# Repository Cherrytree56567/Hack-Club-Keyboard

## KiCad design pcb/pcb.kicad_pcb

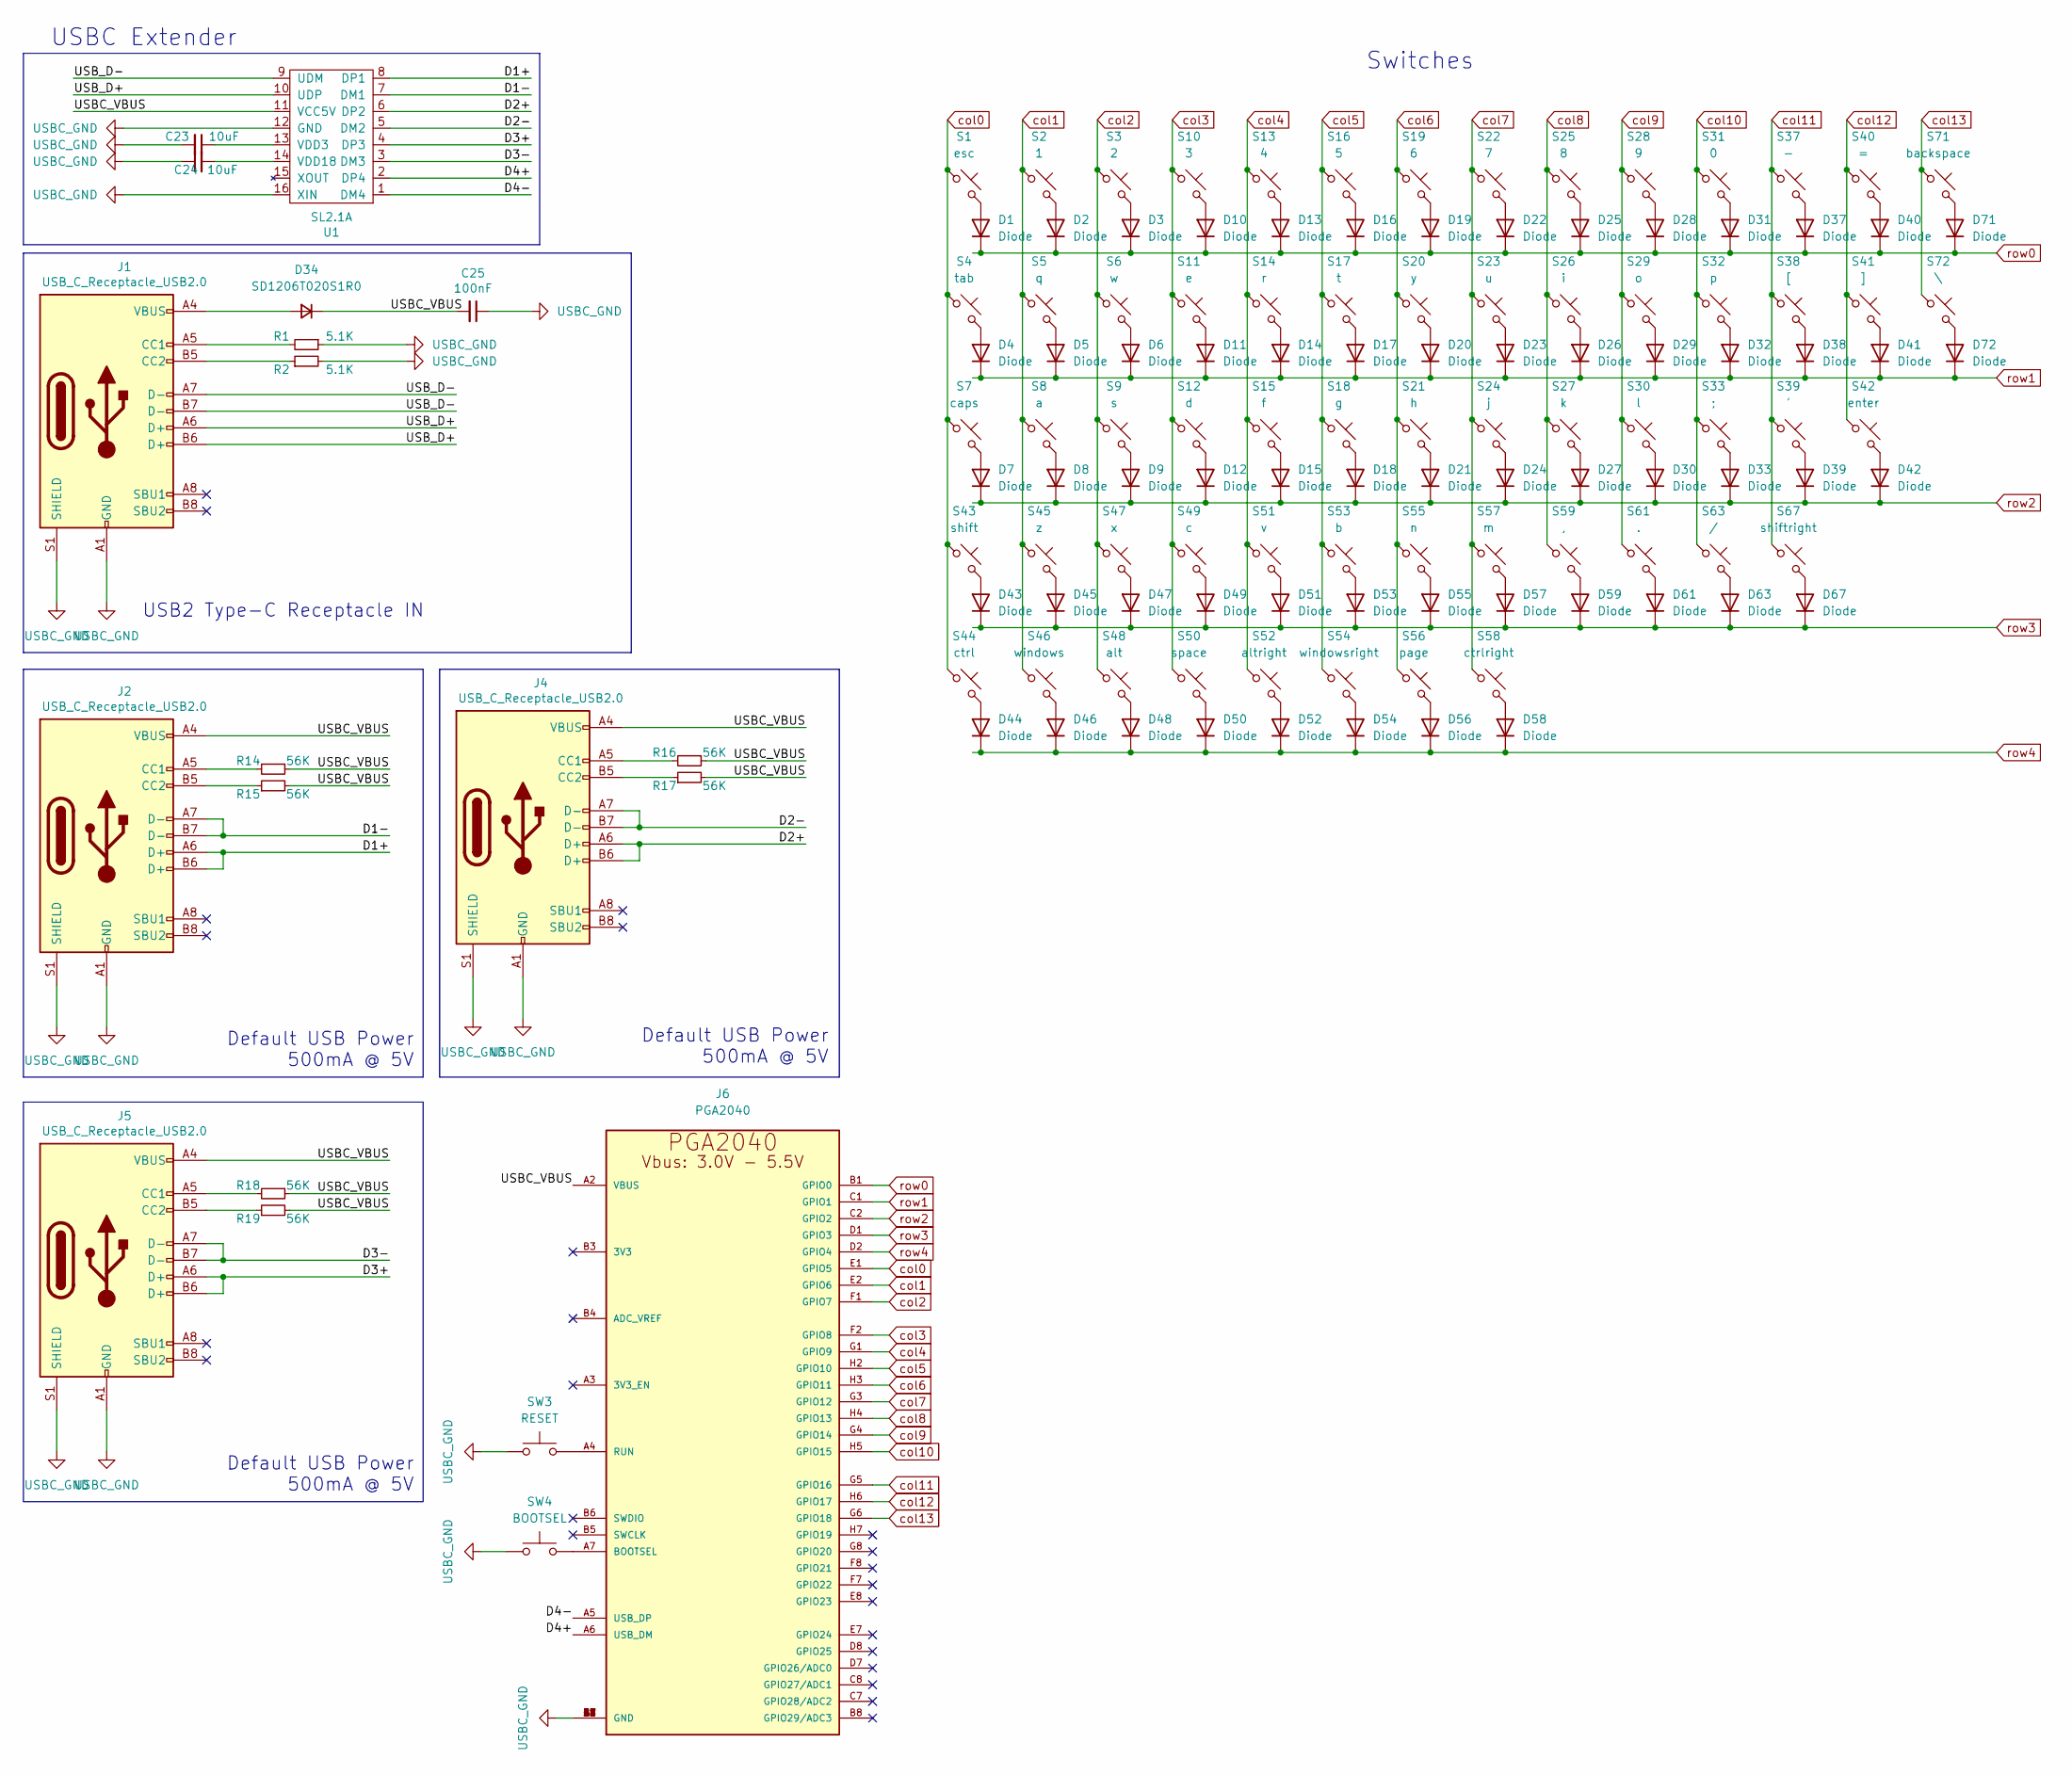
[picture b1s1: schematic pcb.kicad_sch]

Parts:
C23, C24: 10uF; C_0805_2012Metric_Pad1.18x1.45mm_HandSolder
C25: 100nF; C_0805_2012Metric_Pad1.18x1.45mm_HandSolder
D1, D2, D3, D4, D5, D6, D7, D8, D9, D10, D11, D12, D13, D14, D15, D16, D17, D18, D19, D20, D21, D22, D23, D24, D25, D26, D27, D28, D29, D30, D31, D32, D33, D37, D38, D39, D40, D41, D42, D43, D44, D45, D46, D47, D48, D49, D50, D51, D52, D53, D54, D55, D56, D57, D58, D59, D61, D63, D67, D71, D72: Diode; Diode_DO-35
D34: SD1206T020S1R0; D_1206_3216Metric_Pad1.42x1.75mm_HandSolder
J1, J2, J4, J5: USB_C_Receptacle_USB2.0; USB_C_Receptacle_HRO_TYPE-C-31-M-12
J6: PGA2040; PGA2040_PTH_NO_SLOT
R1, R2: 5.1K; R_0805_2012Metric_Pad1.20x1.40mm_HandSolder
R14, R15, R16, R17, R18, R19: 56K; R_0805_2012Metric_Pad1.20x1.40mm_HandSolder
S1: esc; MX_PCB_1.00u
S2: 1; MX_PCB_1.00u
S3: 2; MX_PCB_1.00u
S4: tab; MX_PCB_1.00u
S5: q; MX_PCB_1.00u
S6: w; MX_PCB_1.00u
S7: caps; MX_PCB_1.00u
S8: a; MX_PCB_1.00u
S9: s; MX_PCB_1.00u
S10: 3; MX_PCB_1.00u
S11: e; MX_PCB_1.00u
S12: d; MX_PCB_1.00u
S13: 4; MX_PCB_1.00u
S14: r; MX_PCB_1.00u
S15: f; MX_PCB_1.00u
S16: 5; MX_PCB_1.00u
S17: t; MX_PCB_1.00u
S18: g; MX_PCB_1.00u
S19: 6; MX_PCB_1.00u
S20: y; MX_PCB_1.00u
S21: h; MX_PCB_1.00u
S22: 7; MX_PCB_1.00u
S23: u; MX_PCB_1.00u
S24: j; MX_PCB_1.00u
S25: 8; MX_PCB_1.00u
S26: i; MX_PCB_1.00u
S27: k; MX_PCB_1.00u
S28: 9; MX_PCB_1.00u
S29: o; MX_PCB_1.00u
S30: l; MX_PCB_1.00u
S31: 0; MX_PCB_1.00u
S32: p; MX_PCB_1.00u
S33: ;; MX_PCB_1.00u
S37: -; MX_PCB_1.00u
S38: [; MX_PCB_1.00u
S39: '; MX_PCB_1.00u
S40: =; MX_PCB_1.00u
S41: ]; MX_PCB_1.00u
S42: enter; MX_PCB_1.00u
S43: shift; MX_PCB_1.00u
S44: ctrl; MX_PCB_1.00u
S45: z; MX_PCB_1.00u
S46: windows; MX_PCB_1.00u
S47: x; MX_PCB_1.00u
S48: alt; MX_PCB_1.00u
S49: c; MX_PCB_1.00u
S50: space; MX_PCB_1.00u
S51: v; MX_PCB_1.00u
S52: altright; MX_PCB_1.00u
S53: b; MX_PCB_1.00u
S54: windowsright; MX_PCB_1.00u
S55: n; MX_PCB_1.00u
S56: page; MX_PCB_1.00u
S57: m; MX_PCB_1.00u
S58: ctrlright; MX_PCB_1.00u
S59: ,; MX_PCB_1.00u
S61: .; MX_PCB_1.00u
S63: /; MX_PCB_1.00u
S67: shiftright; MX_PCB_1.00u
S71: backspace; MX_PCB_1.00u
S72: \; MX_PCB_1.00u
SW3: RESET; SW_Push_1P1T_NO_Vertical_Wuerth_434133025816
SW4: BOOTSEL; SW_Push_1P1T_NO_Vertical_Wuerth_434133025816
U1: SL2.1A; SOIC-16_4.55x10.3mm_P1.27mm

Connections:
/D1+: J2.A6 (D+), J2.B6 (D+), U1.8 (DP1)
/D1-: J2.A7 (D-), J2.B7 (D-), U1.7 (DM1)
/D2+: J4.A6 (D+), J4.B6 (D+), U1.6 (DP2)
/D2-: J4.A7 (D-), J4.B7 (D-), U1.5 (DM2)
/D3+: J5.A6 (D+), J5.B6 (D+), U1.4 (DP3)
/D3-: J5.A7 (D-), J5.B7 (D-), U1.3 (DM3)
/D4+: J6.A6 (USB_DM), U1.2 (DP4)
/D4-: J6.A5 (USB_DP), U1.1 (DM4)
/USBC_VBUS: C25.2, D34.1 (K), J2.A4 (VBUS), J2.A9 (VBUS), J2.B4 (VBUS), J2.B9 (VBUS), J4.A4 (VBUS), J4.A9 (VBUS), J4.B4 (VBUS), J4.B9 (VBUS), J5.A4 (VBUS), J5.A9 (VBUS), J5.B4 (VBUS), J5.B9 (VBUS), J6.A2 (VBUS), R14.1, R15.2, R16.1, R17.2, R18.1, R19.2, U1.11 (VCC5V)
/USB_D+: J1.A6 (D+), J1.B6 (D+), U1.10 (UDP)
/USB_D-: J1.A7 (D-), J1.B7 (D-), U1.9 (UDM)
unnamed: D1.2 (A), S1.2
unnamed: D2.2 (A), S2.2
unnamed: D3.2 (A), S3.2
unnamed: D4.2 (A), S4.2
unnamed: D5.2 (A), S5.2
unnamed: D6.2 (A), S6.2
unnamed: D7.2 (A), S7.2
unnamed: D8.2 (A), S8.2
unnamed: D9.2 (A), S9.2
unnamed: D10.2 (A), S10.2
unnamed: D11.2 (A), S11.2
unnamed: D12.2 (A), S12.2
unnamed: D13.2 (A), S13.2
unnamed: D14.2 (A), S14.2
unnamed: D15.2 (A), S15.2
unnamed: D16.2 (A), S16.2
unnamed: D17.2 (A), S17.2
unnamed: D18.2 (A), S18.2
unnamed: D19.2 (A), S19.2
unnamed: D20.2 (A), S20.2
unnamed: D21.2 (A), S21.2
unnamed: D22.2 (A), S22.2
unnamed: D23.2 (A), S23.2
unnamed: D24.2 (A), S24.2
unnamed: D25.2 (A), S25.2
unnamed: D26.2 (A), S26.2
unnamed: D27.2 (A), S27.2
unnamed: D28.2 (A), S28.2
unnamed: D29.2 (A), S29.2
unnamed: D30.2 (A), S30.2
unnamed: D31.2 (A), S31.2
unnamed: D32.2 (A), S32.2
unnamed: D33.2 (A), S33.2
unnamed: D34.2 (A), J1.A4 (VBUS), J1.A9 (VBUS), J1.B4 (VBUS), J1.B9 (VBUS)
unnamed: D37.2 (A), S37.2
unnamed: D38.2 (A), S38.2
unnamed: D39.2 (A), S39.2
unnamed: D40.2 (A), S40.2
unnamed: D41.2 (A), S41.2
unnamed: D42.2 (A), S42.2
unnamed: D43.2 (A), S43.2
unnamed: D44.2 (A), S44.2
unnamed: D45.2 (A), S45.2
unnamed: D46.2 (A), S46.2
unnamed: D47.2 (A), S47.2
unnamed: D48.2 (A), S48.2
unnamed: D49.2 (A), S49.2
unnamed: D50.2 (A), S50.2
unnamed: D51.2 (A), S51.2
unnamed: D52.2 (A), S52.2
unnamed: D53.2 (A), S53.2
unnamed: D54.2 (A), S54.2
unnamed: D55.2 (A), S55.2
unnamed: D56.2 (A), S56.2
unnamed: D57.2 (A), S57.2
unnamed: D58.2 (A), S58.2
unnamed: D59.2 (A), S59.2
unnamed: D61.2 (A), S61.2
unnamed: D63.2 (A), S63.2
unnamed: D67.2 (A), S67.2
unnamed: D71.2 (A), S71.2
unnamed: D72.2 (A), S72.2
unnamed: J1.A5 (CC1), R1.2
unnamed: J1.B5 (CC2), R2.1
unnamed: J2.A5 (CC1), R14.2
unnamed: J2.B5 (CC2), R15.1
unnamed: J4.A5 (CC1), R16.2
unnamed: J4.B5 (CC2), R17.1
unnamed: J5.A5 (CC1), R18.2
unnamed: J5.B5 (CC2), R19.1
unnamed: J6.A7 (BOOTSEL), SW4.2
unnamed: J6.A4 (RUN), SW3.2
unnamed: C23.1, U1.13 (VDD3)
unnamed: C24.2, U1.14 (VDD18)
USBC_GND: C23.2, C24.1, C25.1, J1.A1 (GND), J1.A12 (GND), J1.B1 (GND), J1.B12 (GND), J1.S1 (SHIELD), J2.A1 (GND), J2.A12 (GND), J2.B1 (GND), J2.B12 (GND), J2.S1 (SHIELD), J4.A1 (GND), J4.A12 (GND), J4.B1 (GND), J4.B12 (GND), J4.S1 (SHIELD), J5.A1 (GND), J5.A12 (GND), J5.B1 (GND), J5.B12 (GND), J5.S1 (SHIELD), J6.A1 (GND), J6.A8 (GND), J6.B2 (GND), J6.B7 (GND), J6.G2 (GND), J6.G7 (GND), J6.H1 (GND), J6.H8 (GND), R1.1, R2.2, SW3.1, SW4.1, U1.12 (GND), U1.16 (XIN)
col0: J6.E1 (GPIO5), S1.1, S4.1, S7.1, S43.1, S44.1
col1: J6.E2 (GPIO6), S2.1, S5.1, S8.1, S45.1, S46.1
col2: J6.F1 (GPIO7), S3.1, S6.1, S9.1, S47.1, S48.1
col3: J6.F2 (GPIO8), S10.1, S11.1, S12.1, S49.1, S50.1
col4: J6.G1 (GPIO9), S13.1, S14.1, S15.1, S51.1, S52.1
col5: J6.H2 (GPIO10), S16.1, S17.1, S18.1, S53.1, S54.1
col6: J6.H3 (GPIO11), S19.1, S20.1, S21.1, S55.1, S56.1
col7: J6.G3 (GPIO12), S22.1, S23.1, S24.1, S57.1, S58.1
col8: J6.H4 (GPIO13), S25.1, S26.1, S27.1, S59.1
col9: J6.G4 (GPIO14), S28.1, S29.1, S30.1, S61.1
col10: J6.H5 (GPIO15), S31.1, S32.1, S33.1, S63.1
col11: J6.G5 (GPIO16), S37.1, S38.1, S39.1, S67.1
col12: J6.H6 (GPIO17), S40.1, S41.1, S42.1
col13: J6.G6 (GPIO18), S71.1, S72.1
row0: D1.1 (K), D2.1 (K), D3.1 (K), D10.1 (K), D13.1 (K), D16.1 (K), D19.1 (K), D22.1 (K), D25.1 (K), D28.1 (K), D31.1 (K), D37.1 (K), D40.1 (K), D71.1 (K), J6.B1 (GPIO0)
row1: D4.1 (K), D5.1 (K), D6.1 (K), D11.1 (K), D14.1 (K), D17.1 (K), D20.1 (K), D23.1 (K), D26.1 (K), D29.1 (K), D32.1 (K), D38.1 (K), D41.1 (K), D72.1 (K), J6.C1 (GPIO1)
row2: D7.1 (K), D8.1 (K), D9.1 (K), D12.1 (K), D15.1 (K), D18.1 (K), D21.1 (K), D24.1 (K), D27.1 (K), D30.1 (K), D33.1 (K), D39.1 (K), D42.1 (K), J6.C2 (GPIO2)
row3: D43.1 (K), D45.1 (K), D47.1 (K), D49.1 (K), D51.1 (K), D53.1 (K), D55.1 (K), D57.1 (K), D59.1 (K), D61.1 (K), D63.1 (K), D67.1 (K), J6.D1 (GPIO3)
row4: D44.1 (K), D46.1 (K), D48.1 (K), D50.1 (K), D52.1 (K), D54.1 (K), D56.1 (K), D58.1 (K), J6.D2 (GPIO4)

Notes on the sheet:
Default USB Power 500mA @ 5V
USBC Extender
Switches
USB2 Type-C Receptacle IN

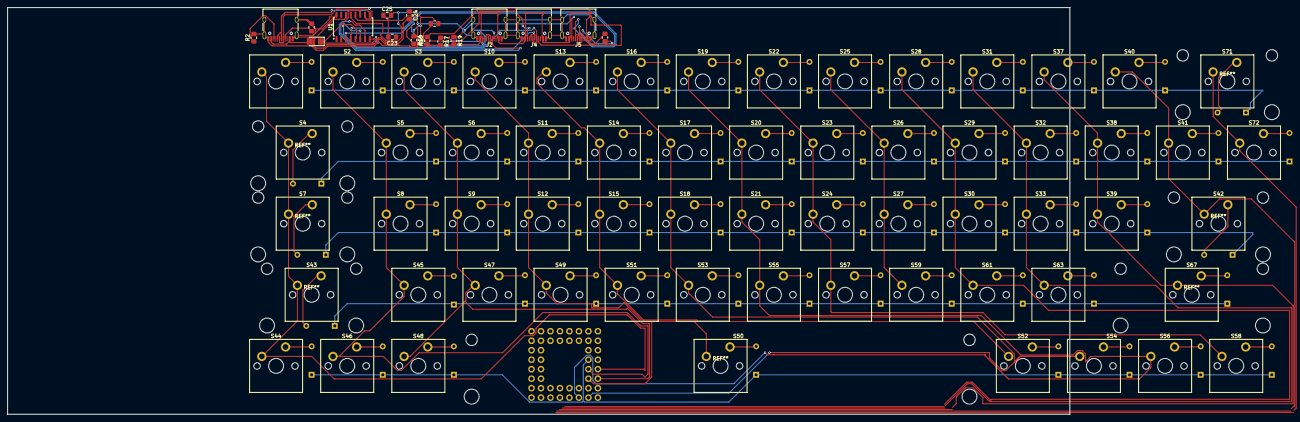
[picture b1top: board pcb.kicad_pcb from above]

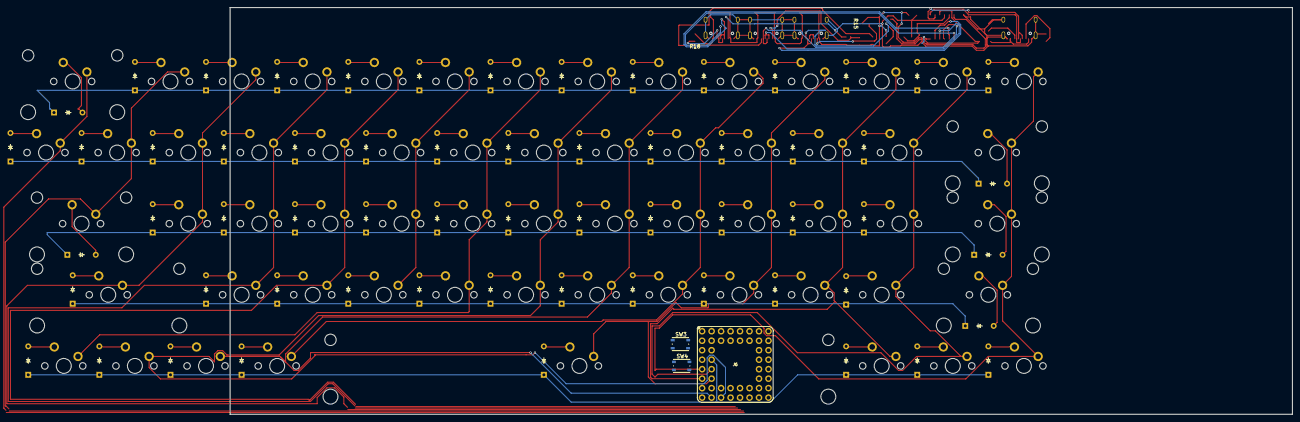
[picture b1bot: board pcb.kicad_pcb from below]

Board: 2 copper layers, 284.6 x 108.9 mm, 142 parts (64 on the bottom side), 105 nets.

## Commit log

2025-01-30 still making the full 72 sized keyboard pcb
2025-02-03 New Wires
